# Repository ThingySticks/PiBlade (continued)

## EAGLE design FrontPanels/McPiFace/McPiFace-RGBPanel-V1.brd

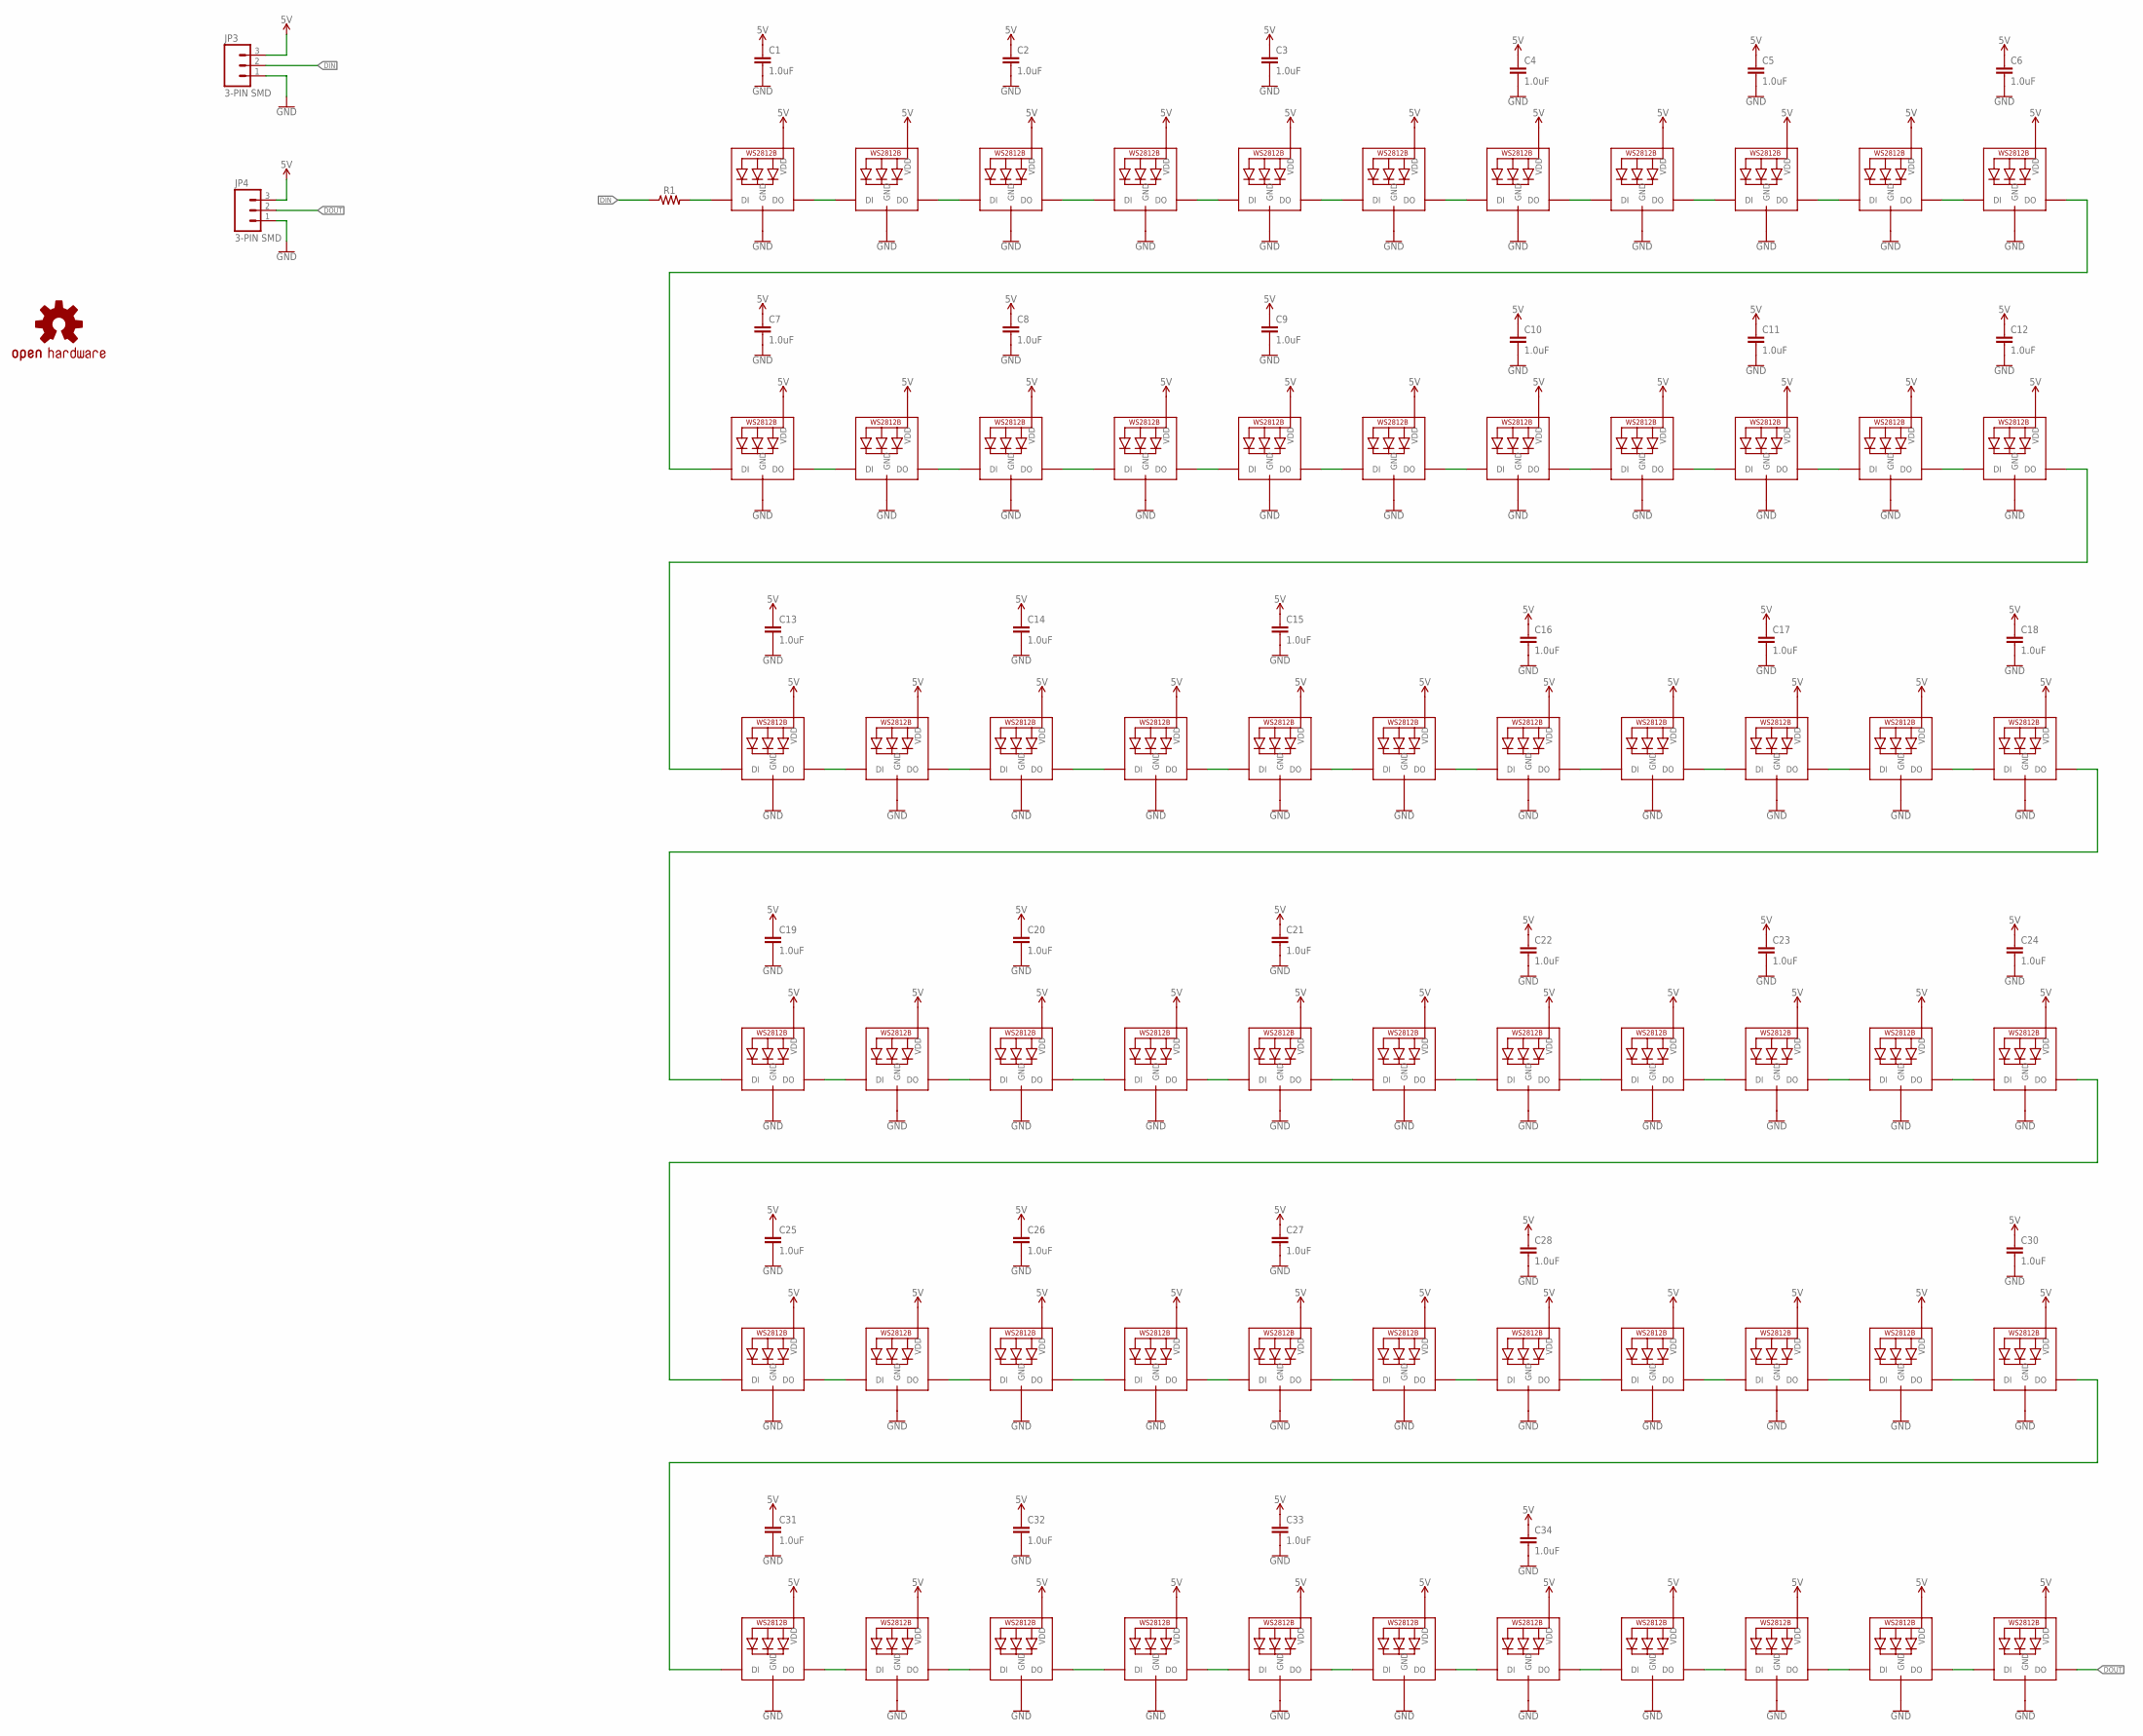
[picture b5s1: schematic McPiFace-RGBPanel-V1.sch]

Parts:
C1, C2, C3, C4, C5, C6, C7, C8, C9, C10, C11, C12, C13, C14, C15, C16, C17, C18, C19, C20, C21, C22, C23, C24, C25, C26, C27, C28, C30, C31, C32, C33, C34: 1.0uF; 0805-CAP
JP3, JP4: 3-PIN SMD; JST-3-SMD
LED1, LED2, LED3, LED4, LED5, LED6, LED7, LED8, LED9, LED10, LED11, LED12, LED13, LED14, LED15, LED16, LED17, LED18, LED19, LED20, LED21, LED22, LED23, LED24, LED25, LED26, LED27, LED28, LED29, LED30, LED31, LED32, LED33, LED34, LED35, LED36, LED37, LED38, LED39, LED40, LED41, LED42, LED43, LED44, LED45, LED46, LED47, LED48, LED49, LED50, LED51, LED52, LED53, LED54, LED55, LED56, LED57, LED58, LED59, LED60, LED61, LED62, LED63, LED64, LED65, LED66: WS2812B5050; WS2812B
LOGO1: OSHW-LOGOL; OSHW-LOGO-L
R1: 0805

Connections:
5V: C1.1, C2.1, C3.1, C4.1, C5.1, C6.1, C7.1, C8.1, C9.1, C10.1, C11.1, C12.1, C13.1, C14.1, C15.1, C16.1, C17.1, C18.1, C19.1, C20.1, C21.1, C22.1, C23.1, C24.1, C25.1, C26.1, C27.1, C28.1, C30.1, C31.1, C32.1, C33.1, C34.1, JP3.3, JP4.3, LED1.1-VDD (VDD), LED2.1-VDD (VDD), LED3.1-VDD (VDD), LED4.1-VDD (VDD), LED5.1-VDD (VDD), LED6.1-VDD (VDD), LED7.1-VDD (VDD), LED8.1-VDD (VDD), LED9.1-VDD (VDD), LED10.1-VDD (VDD), LED11.1-VDD (VDD), LED12.1-VDD (VDD), LED13.1-VDD (VDD), LED14.1-VDD (VDD), LED15.1-VDD (VDD), LED16.1-VDD (VDD), LED17.1-VDD (VDD), LED18.1-VDD (VDD), LED19.1-VDD (VDD), LED20.1-VDD (VDD), LED21.1-VDD (VDD), LED22.1-VDD (VDD), LED23.1-VDD (VDD), LED24.1-VDD (VDD), LED25.1-VDD (VDD), LED26.1-VDD (VDD), LED27.1-VDD (VDD), LED28.1-VDD (VDD), LED29.1-VDD (VDD), LED30.1-VDD (VDD), LED31.1-VDD (VDD), LED32.1-VDD (VDD), LED33.1-VDD (VDD), LED34.1-VDD (VDD), LED35.1-VDD (VDD), LED36.1-VDD (VDD), LED37.1-VDD (VDD), LED38.1-VDD (VDD), LED39.1-VDD (VDD), LED40.1-VDD (VDD), LED41.1-VDD (VDD), LED42.1-VDD (VDD), LED43.1-VDD (VDD), LED44.1-VDD (VDD), LED45.1-VDD (VDD), LED46.1-VDD (VDD), LED47.1-VDD (VDD), LED48.1-VDD (VDD), LED49.1-VDD (VDD), LED50.1-VDD (VDD), LED51.1-VDD (VDD), LED52.1-VDD (VDD), LED53.1-VDD (VDD), LED54.1-VDD (VDD), LED55.1-VDD (VDD), LED56.1-VDD (VDD), LED57.1-VDD (VDD), LED58.1-VDD (VDD), LED59.1-VDD (VDD), LED60.1-VDD (VDD), LED61.1-VDD (VDD), LED62.1-VDD (VDD), LED63.1-VDD (VDD), LED64.1-VDD (VDD), LED65.1-VDD (VDD), LED66.1-VDD (VDD)
DIN: JP3.2, R1.1
DOUT: JP4.2, LED66.2-DOUT (DO)
GND: C1.2, C2.2, C3.2, C4.2, C5.2, C6.2, C7.2, C8.2, C9.2, C10.2, C11.2, C12.2, C13.2, C14.2, C15.2, C16.2, C17.2, C18.2, C19.2, C20.2, C21.2, C22.2, C23.2, C24.2, C25.2, C26.2, C27.2, C28.2, C30.2, C31.2, C32.2, C33.2, C34.2, JP3.1, JP4.1, LED1.3-GND (GND), LED2.3-GND (GND), LED3.3-GND (GND), LED4.3-GND (GND), LED5.3-GND (GND), LED6.3-GND (GND), LED7.3-GND (GND), LED8.3-GND (GND), LED9.3-GND (GND), LED10.3-GND (GND), LED11.3-GND (GND), LED12.3-GND (GND), LED13.3-GND (GND), LED14.3-GND (GND), LED15.3-GND (GND), LED16.3-GND (GND), LED17.3-GND (GND), LED18.3-GND (GND), LED19.3-GND (GND), LED20.3-GND (GND), LED21.3-GND (GND), LED22.3-GND (GND), LED23.3-GND (GND), LED24.3-GND (GND), LED25.3-GND (GND), LED26.3-GND (GND), LED27.3-GND (GND), LED28.3-GND (GND), LED29.3-GND (GND), LED30.3-GND (GND), LED31.3-GND (GND), LED32.3-GND (GND), LED33.3-GND (GND), LED34.3-GND (GND), LED35.3-GND (GND), LED36.3-GND (GND), LED37.3-GND (GND), LED38.3-GND (GND), LED39.3-GND (GND), LED40.3-GND (GND), LED41.3-GND (GND), LED42.3-GND (GND), LED43.3-GND (GND), LED44.3-GND (GND), LED45.3-GND (GND), LED46.3-GND (GND), LED47.3-GND (GND), LED48.3-GND (GND), LED49.3-GND (GND), LED50.3-GND (GND), LED51.3-GND (GND), LED52.3-GND (GND), LED53.3-GND (GND), LED54.3-GND (GND), LED55.3-GND (GND), LED56.3-GND (GND), LED57.3-GND (GND), LED58.3-GND (GND), LED59.3-GND (GND), LED60.3-GND (GND), LED61.3-GND (GND), LED62.3-GND (GND), LED63.3-GND (GND), LED64.3-GND (GND), LED65.3-GND (GND), LED66.3-GND (GND)
unnamed: LED1.2-DOUT (DO), LED2.4-DIN (DI)
unnamed: LED11.2-DOUT (DO), LED12.4-DIN (DI)
unnamed: LED12.2-DOUT (DO), LED13.4-DIN (DI)
unnamed: LED13.2-DOUT (DO), LED14.4-DIN (DI)
unnamed: LED1.4-DIN (DI), R1.2
unnamed: LED14.2-DOUT (DO), LED15.4-DIN (DI)
unnamed: LED15.2-DOUT (DO), LED16.4-DIN (DI)
unnamed: LED2.2-DOUT (DO), LED3.4-DIN (DI)
unnamed: LED3.2-DOUT (DO), LED4.4-DIN (DI)
unnamed: LED16.2-DOUT (DO), LED17.4-DIN (DI)
unnamed: LED4.2-DOUT (DO), LED5.4-DIN (DI)
unnamed: LED5.2-DOUT (DO), LED6.4-DIN (DI)
unnamed: LED6.2-DOUT (DO), LED7.4-DIN (DI)
unnamed: LED7.2-DOUT (DO), LED8.4-DIN (DI)
unnamed: LED8.2-DOUT (DO), LED9.4-DIN (DI)
unnamed: LED9.2-DOUT (DO), LED10.4-DIN (DI)
unnamed: LED10.2-DOUT (DO), LED11.4-DIN (DI)
unnamed: LED17.2-DOUT (DO), LED18.4-DIN (DI)
unnamed: LED18.2-DOUT (DO), LED19.4-DIN (DI)
unnamed: LED19.2-DOUT (DO), LED20.4-DIN (DI)
unnamed: LED20.2-DOUT (DO), LED21.4-DIN (DI)
unnamed: LED21.2-DOUT (DO), LED22.4-DIN (DI)
unnamed: LED22.2-DOUT (DO), LED23.4-DIN (DI)
unnamed: LED23.2-DOUT (DO), LED24.4-DIN (DI)
unnamed: LED24.2-DOUT (DO), LED25.4-DIN (DI)
unnamed: LED25.2-DOUT (DO), LED26.4-DIN (DI)
unnamed: LED26.2-DOUT (DO), LED27.4-DIN (DI)
unnamed: LED27.2-DOUT (DO), LED28.4-DIN (DI)
unnamed: LED28.2-DOUT (DO), LED29.4-DIN (DI)
unnamed: LED29.2-DOUT (DO), LED30.4-DIN (DI)
unnamed: LED30.2-DOUT (DO), LED31.4-DIN (DI)
unnamed: LED31.2-DOUT (DO), LED32.4-DIN (DI)
unnamed: LED32.2-DOUT (DO), LED33.4-DIN (DI)
unnamed: LED33.2-DOUT (DO), LED34.4-DIN (DI)
unnamed: LED34.2-DOUT (DO), LED35.4-DIN (DI)
unnamed: LED35.2-DOUT (DO), LED36.4-DIN (DI)
unnamed: LED36.2-DOUT (DO), LED37.4-DIN (DI)
unnamed: LED37.2-DOUT (DO), LED38.4-DIN (DI)
unnamed: LED38.2-DOUT (DO), LED39.4-DIN (DI)
unnamed: LED39.2-DOUT (DO), LED40.4-DIN (DI)
unnamed: LED40.2-DOUT (DO), LED41.4-DIN (DI)
unnamed: LED41.2-DOUT (DO), LED42.4-DIN (DI)
unnamed: LED42.2-DOUT (DO), LED43.4-DIN (DI)
unnamed: LED43.2-DOUT (DO), LED44.4-DIN (DI)
unnamed: LED44.2-DOUT (DO), LED45.4-DIN (DI)
unnamed: LED45.2-DOUT (DO), LED46.4-DIN (DI)
unnamed: LED46.2-DOUT (DO), LED47.4-DIN (DI)
unnamed: LED47.2-DOUT (DO), LED48.4-DIN (DI)
unnamed: LED48.2-DOUT (DO), LED49.4-DIN (DI)
unnamed: LED49.2-DOUT (DO), LED50.4-DIN (DI)
unnamed: LED50.2-DOUT (DO), LED51.4-DIN (DI)
unnamed: LED51.2-DOUT (DO), LED52.4-DIN (DI)
unnamed: LED52.2-DOUT (DO), LED53.4-DIN (DI)
unnamed: LED53.2-DOUT (DO), LED54.4-DIN (DI)
unnamed: LED54.2-DOUT (DO), LED55.4-DIN (DI)
unnamed: LED55.2-DOUT (DO), LED56.4-DIN (DI)
unnamed: LED56.2-DOUT (DO), LED57.4-DIN (DI)
unnamed: LED57.2-DOUT (DO), LED58.4-DIN (DI)
unnamed: LED58.2-DOUT (DO), LED59.4-DIN (DI)
unnamed: LED59.2-DOUT (DO), LED60.4-DIN (DI)
unnamed: LED60.2-DOUT (DO), LED61.4-DIN (DI)
unnamed: LED61.2-DOUT (DO), LED62.4-DIN (DI)
unnamed: LED62.2-DOUT (DO), LED63.4-DIN (DI)
unnamed: LED63.2-DOUT (DO), LED64.4-DIN (DI)
unnamed: LED64.2-DOUT (DO), LED65.4-DIN (DI)
unnamed: LED65.2-DOUT (DO), LED66.4-DIN (DI)

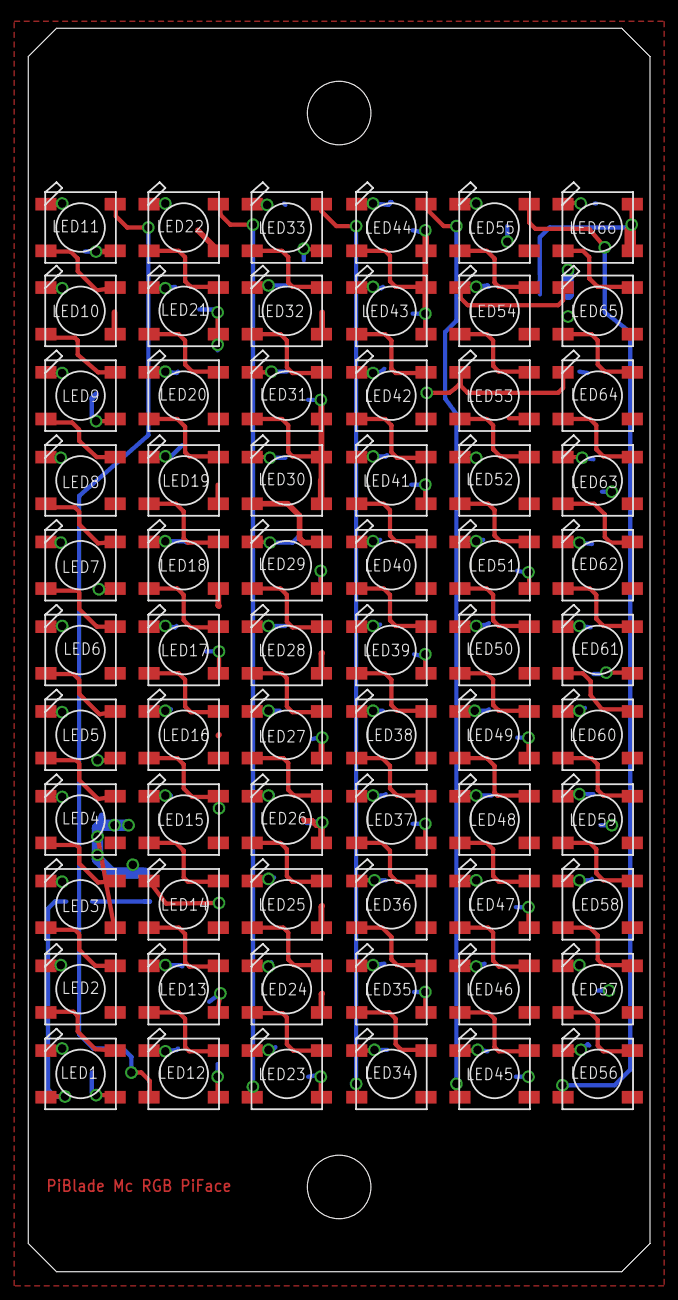
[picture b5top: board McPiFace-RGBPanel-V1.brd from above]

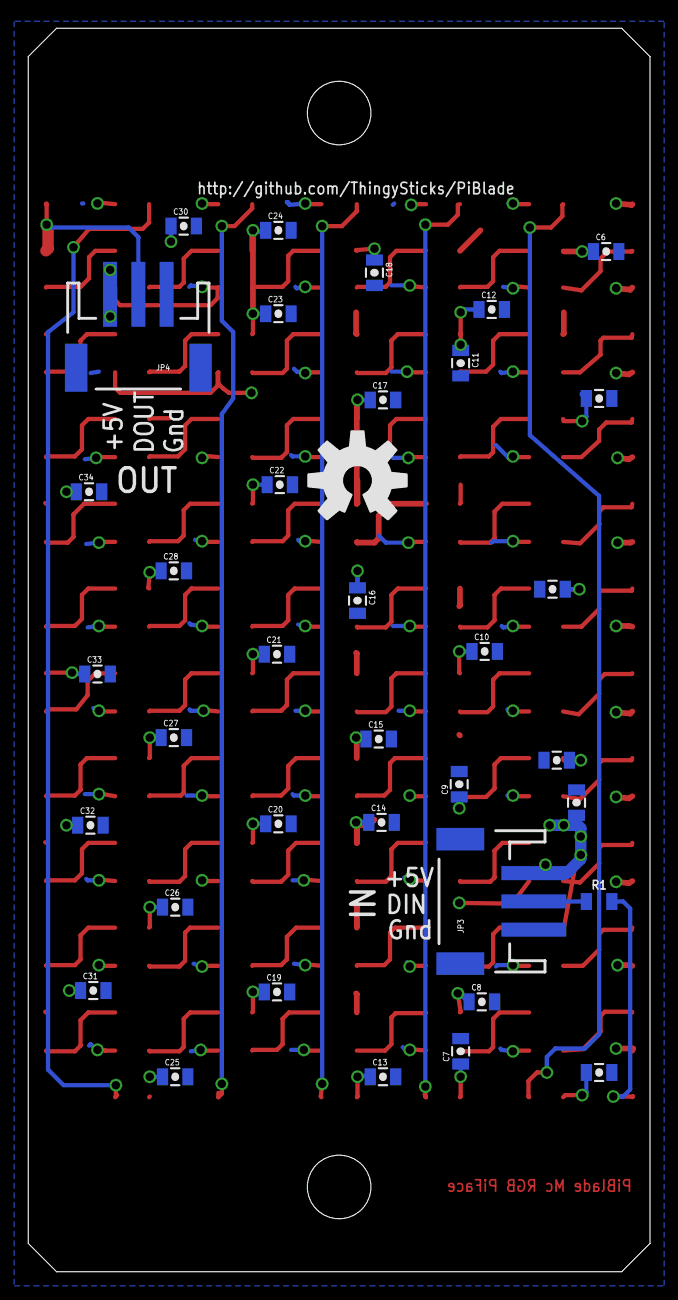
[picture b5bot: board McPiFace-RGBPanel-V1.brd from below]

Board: 2 copper layers, 44.0 x 88.0 mm, 103 parts (37 on the bottom side), 70 nets.

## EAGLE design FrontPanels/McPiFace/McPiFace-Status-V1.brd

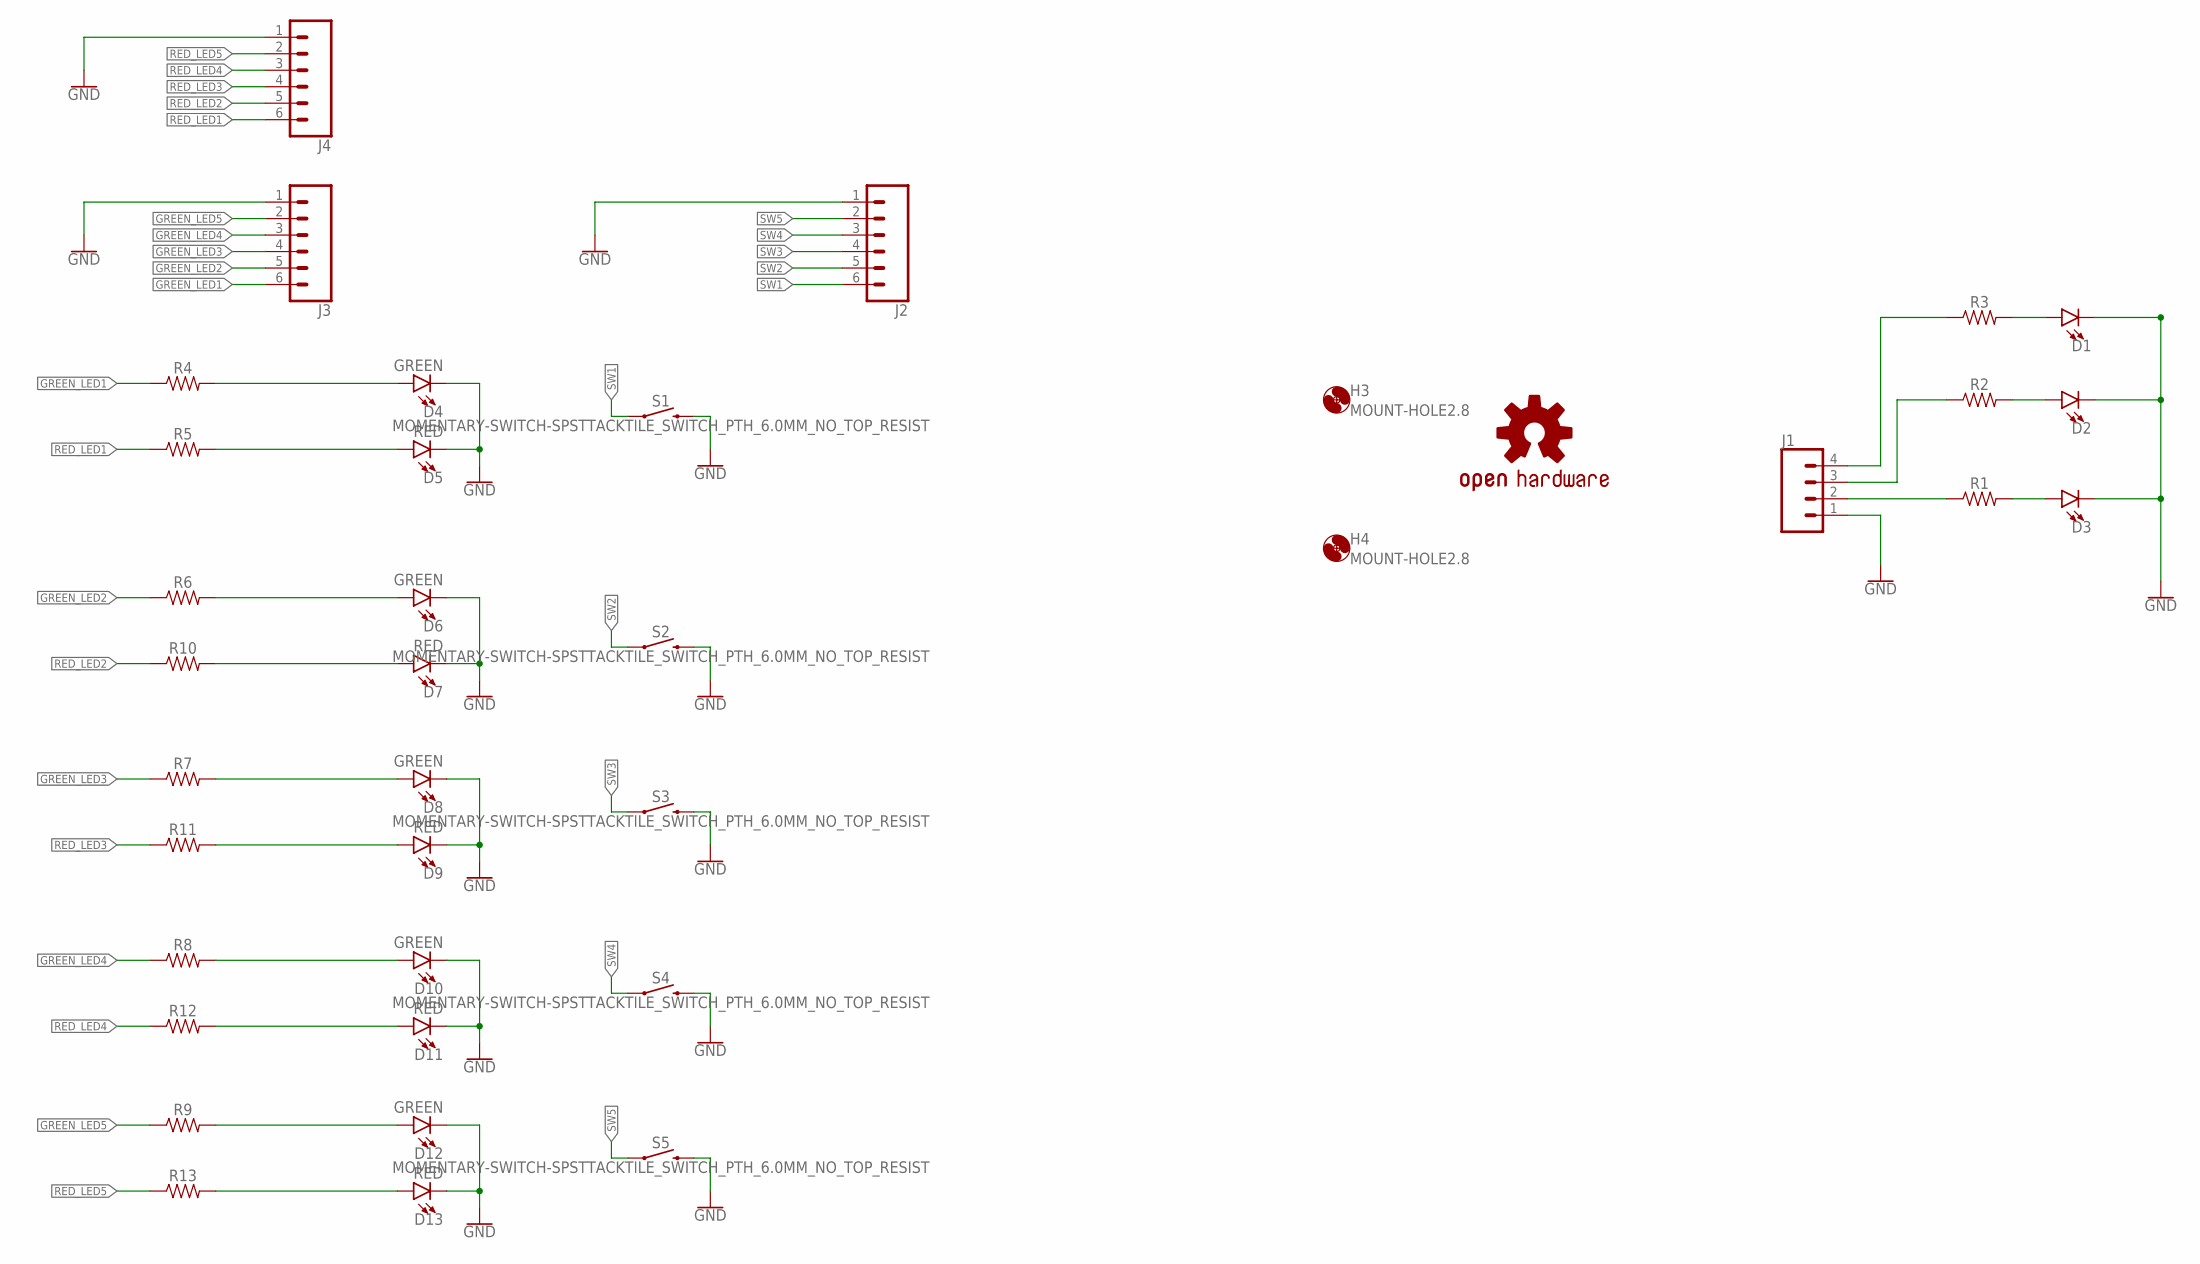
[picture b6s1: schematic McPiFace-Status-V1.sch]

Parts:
D1, D2, D3: LED1206-BOTTOM-1.6MM; LED-1206-BOTTOM-1.6MM
D4, D6, D8, D10, D12: GREEN; LED-1206
D5, D7, D9, D11, D13: RED; LED-1206
H3, H4: MOUNT-HOLE2.8; 2,8
J1: CONN_04SMD2; 1X04_1MM_RA
J2, J3, J4: CONN_06SMD-1MM; 1X06-1MM
LOGO1: OSHW-LOGOL; OSHW-LOGO-L
R1, R2, R3: 1206
R4, R5, R6, R7, R8, R9, R10, R11, R12, R13: 0805
S1, S2, S3, S4, S5: MOMENTARY-SWITCH-SPSTTACKTILE_SWITCH_PTH_6.0MM_NO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; TACTILE_SWITCH_PTH_6.0MM_NO_TOP_RESIST

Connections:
GND: D1.C, D2.C, D3.C, D4.C, D5.C, D6.C, D7.C, D8.C, D9.C, D10.C, D11.C, D12.C, D13.C, J1.1, J2.1, J3.1, J4.1, S1.3 (2), S2.3 (2), S3.3 (2), S4.3 (2), S5.3 (2)
GREEN_LED1: J3.6, R4.1
GREEN_LED2: J3.5, R6.1
GREEN_LED3: J3.4, R7.1
GREEN_LED4: J3.3, R8.1
GREEN_LED5: J3.2, R9.1
unnamed: D4.A, R4.2
unnamed: D1.A, R3.2
unnamed: D2.A, R2.2
unnamed: D3.A, R1.2
unnamed: J1.2, R1.1
unnamed: J1.3, R2.1
unnamed: J1.4, R3.1
unnamed: D6.A, R6.2
unnamed: D12.A, R9.2
unnamed: D10.A, R8.2
unnamed: D8.A, R7.2
unnamed: D5.A, R5.2
unnamed: D7.A, R10.2
unnamed: D9.A, R11.2
unnamed: D11.A, R12.2
unnamed: D13.A, R13.2
RED_LED1: J4.6, R5.1
RED_LED2: J4.5, R10.1
RED_LED3: J4.4, R11.1
RED_LED4: J4.3, R12.1
RED_LED5: J4.2, R13.1
SW1: J2.6, S1.1
SW2: J2.5, S2.1
SW3: J2.4, S3.1
SW4: J2.3, S4.1
SW5: J2.2, S5.1

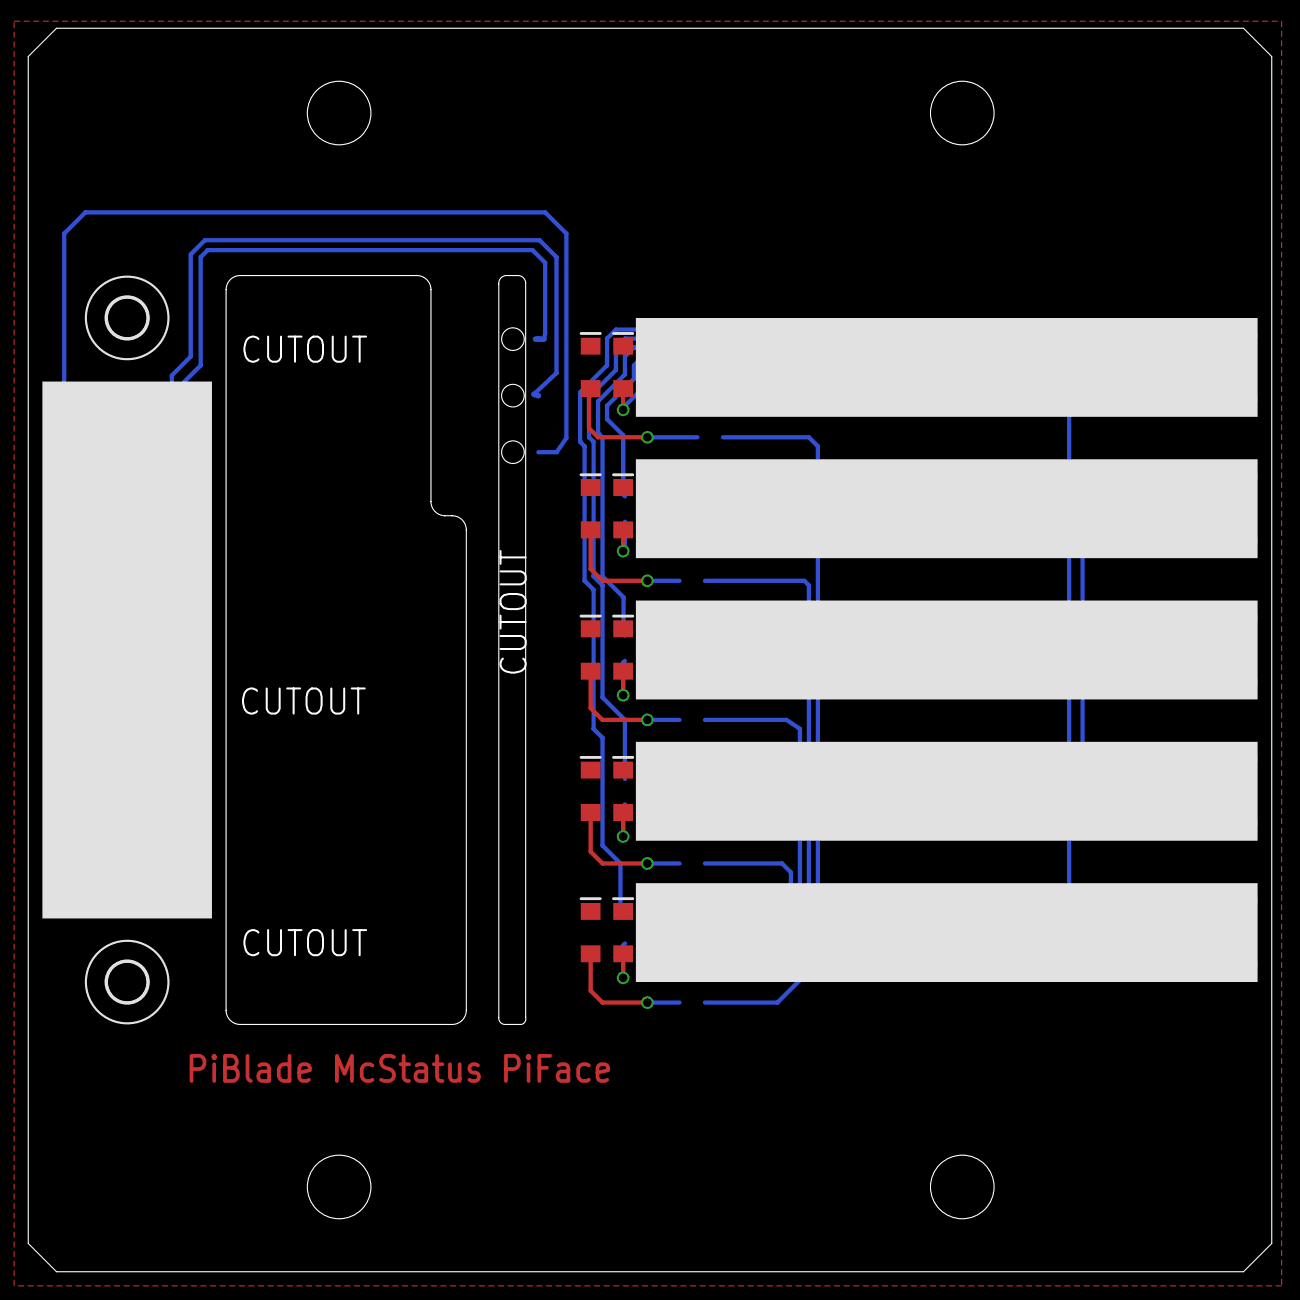
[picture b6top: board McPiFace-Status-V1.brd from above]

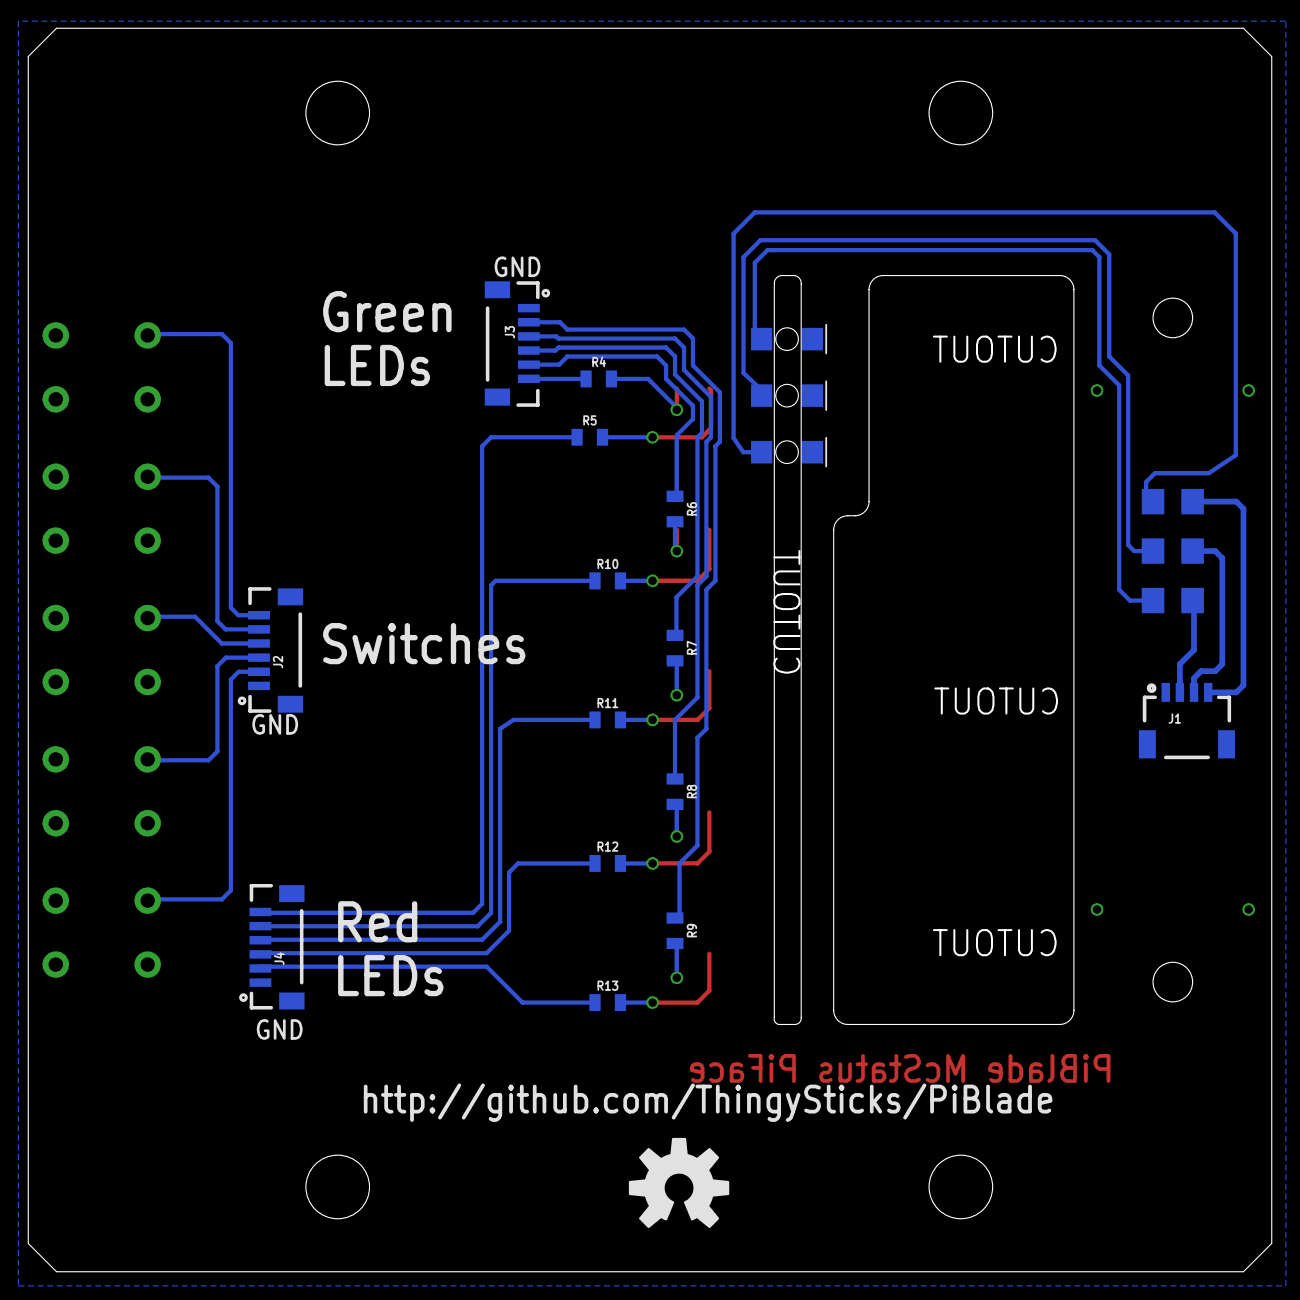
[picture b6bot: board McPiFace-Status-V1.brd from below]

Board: 2 copper layers, 88.0 x 88.0 mm, 38 parts (21 on the bottom side), 32 nets.
